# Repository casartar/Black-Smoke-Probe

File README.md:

# Black Smoke Probe

## Einleitung
Die Black Smoke Probe ist eine Open Source Hardware, die kompatibel ist zur Black Magic Probe v2.1e.

Ich habe den letzten öffentlich zugänglichen [Schaltplan](https://black-magic.org/_downloads/5a984c502435264dc19bc5e08c8b55cd/bmpm_v2_1e_schematic.pdf) genommen und die Micro-USB durch eine USB-C Buchse ersetzt. 

Da die Platine leicht von Hand zu bestücken sein sollte, ist das Layout single sided und einige Bauteile als auch die Diemensions der Platine größer gewählt als beim Original. Diesen Maßnahmen ist die UART zum Opfer gefallen und ist nur noch als Testpoints auf der Bottom Seite verfügbar (Ohne Level-Shifter). 

## Original Firmware
[https://github.com/blackmagic-debug/blackmagic](https://github.com/blackmagic-debug/blackmagic)

## iBOM
[ibom.html](https://html-preview.github.io/?url=https://github.com/casartar/Black-Smoke-Probe/blob/main/Hardware/bom/ibom.html)

## Flashen

### Flashen des Bootloaders
```
st-flash write blackmagic_native_bootloader.bin 0x08000000
```

### Flashen der Applikation
```
dfu-util -d 1d50:6018,:6017 -s 0x08002000:leave -D blackmagic_native_firmware.bin
```

## Testen

[https://github.com/casartar/BlackPillUniversalTester](https://github.com/casartar/BlackPillUniversalTester)

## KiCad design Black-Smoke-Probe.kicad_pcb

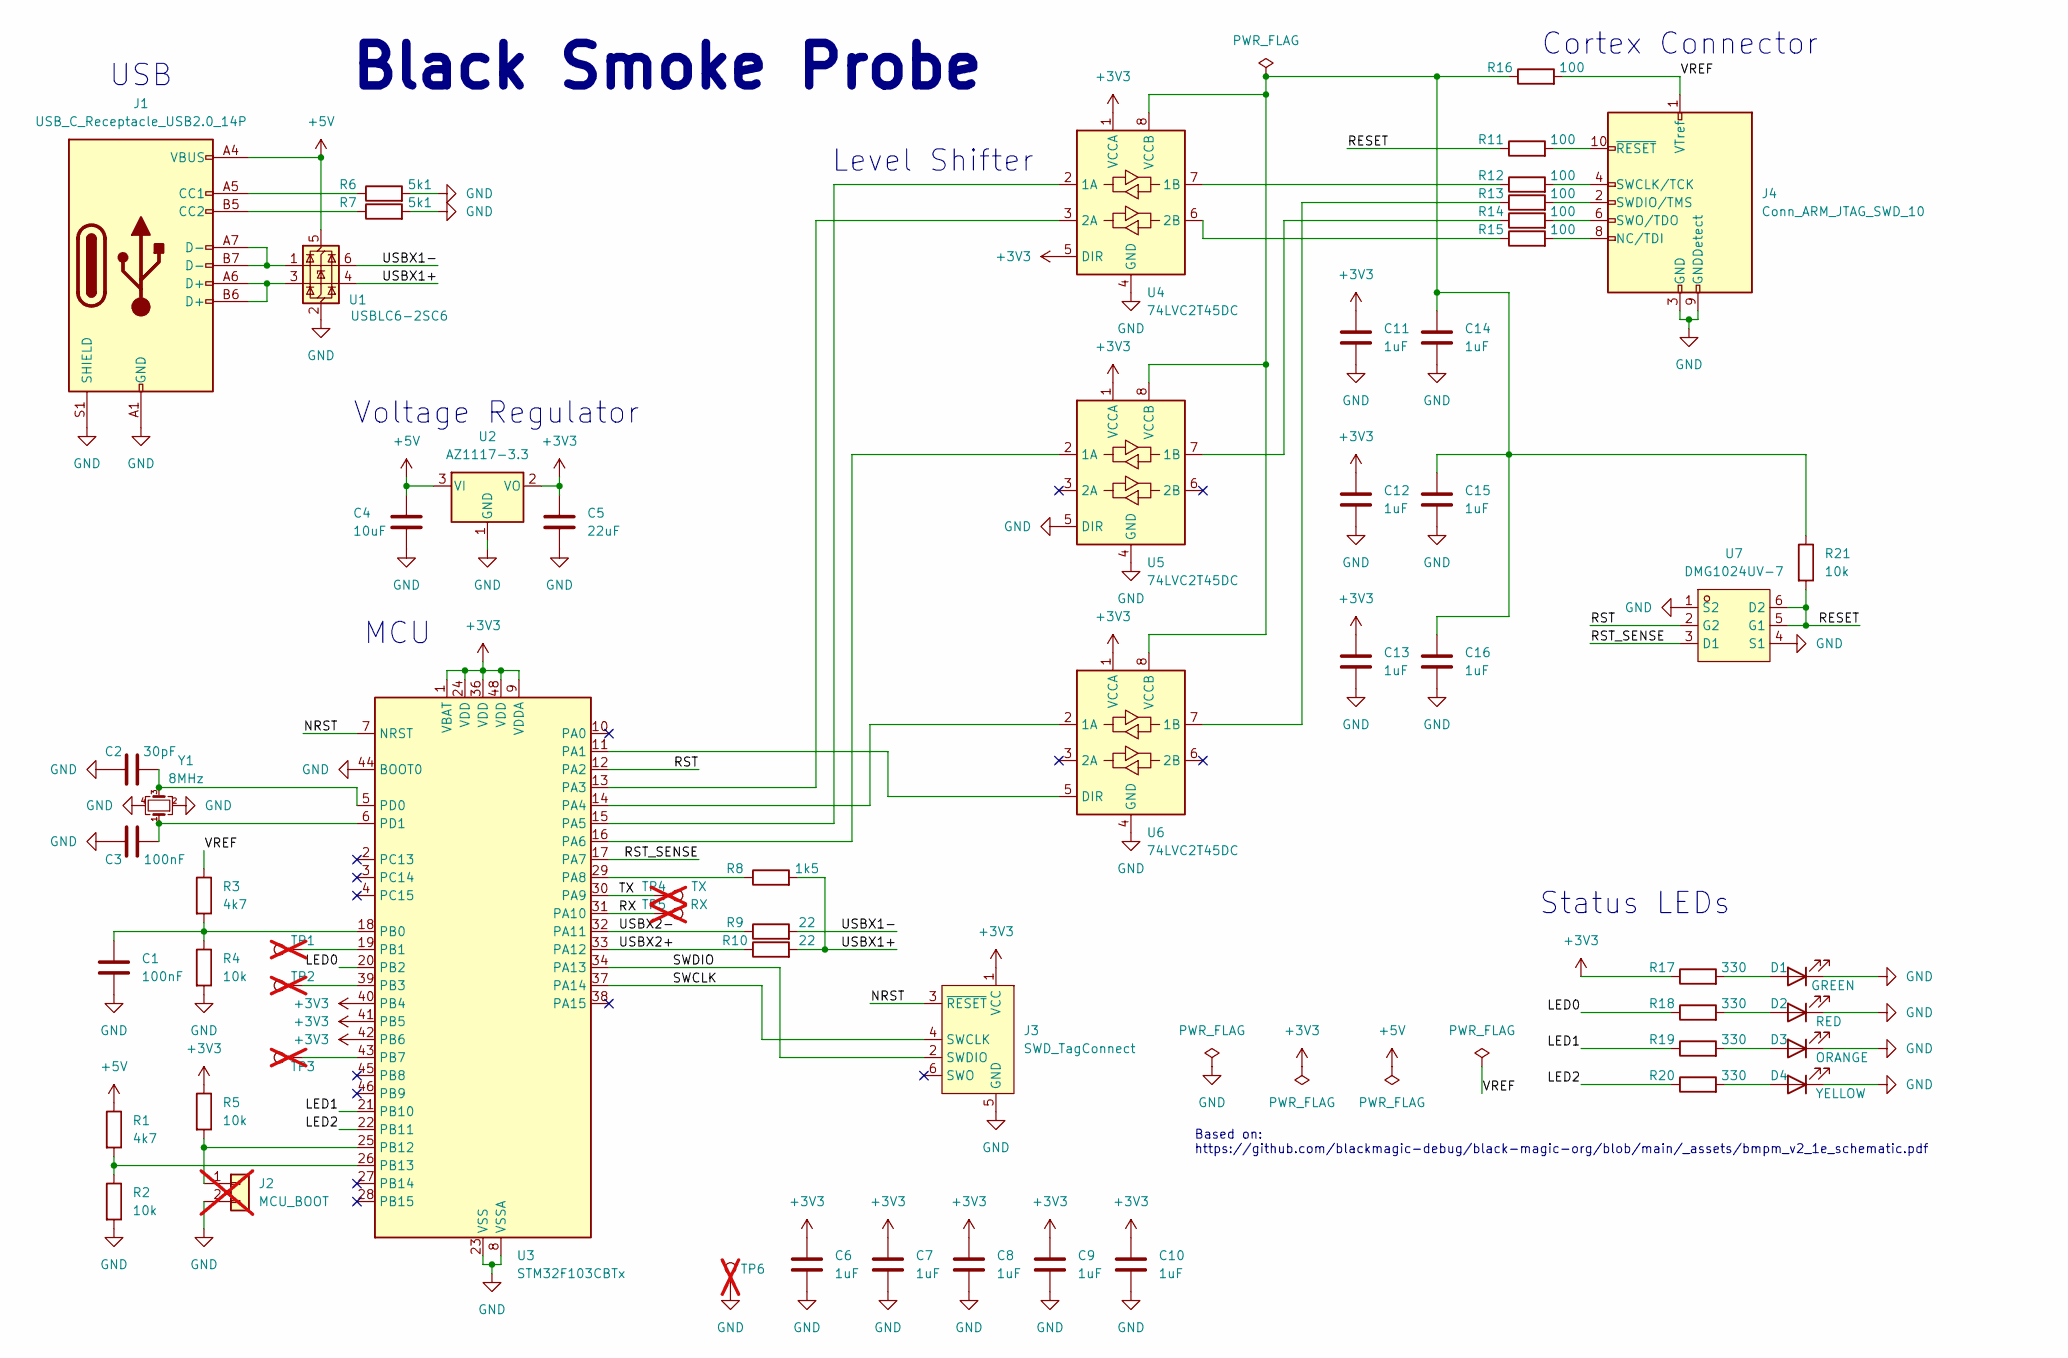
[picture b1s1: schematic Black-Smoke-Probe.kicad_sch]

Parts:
C1, C3: 100nF; C_0603_1608Metric; LCSC Part C14663
C2: 30pF; C_0603_1608Metric; LCSC Part C1658
C4: 10uF; C_0603_1608Metric; LCSC Part C19702
C5: 22uF; C_0603_1608Metric; LCSC Part C86295
C6, C7, C8, C9, C10, C11, C12, C13, C14, C15, C16: 1uF; C_0603_1608Metric; LCSC Part C15849
D1: GREEN; LED_0603_1608Metric; LCSC Part C12065
D2: RED; LED_0603_1608Metric; LCSC Part C157741
D3: ORANGE; LED_0603_1608Metric; LCSC Part C157740
D4: YELLOW; LED_0603_1608Metric; LCSC Part C160477
J1: USB_C_Receptacle_USB2.0_14P; USB_C_Receptacle_HRO_TYPE-C-31-M-12; LCSC Part C165948
J2: MCU_BOOT; PinHeader_1x02_P2.54mm_Vertical; not fitted
J3: SWD_TagConnect; Tag-Connect_TC2030-IDC-NL_2x03_P1.27mm_Vertical
J4: Conn_ARM_JTAG_SWD_10; PinHeader_2x05_P1.27mm_Vertical_SMD; LCSC Part C42372555
R1, R3: 4k7; R_0603_1608Metric; LCSC Part C105428
R2, R4, R5, R21: 10k; R_0603_1608Metric; LCSC Part C98220
R6, R7: 5k1; R_0603_1608Metric; LCSC Part C105580
R8: 1k5; R_0603_1608Metric; LCSC Part C22843
R9, R10: 22; R_0603_1608Metric; LCSC Part C1203
R11, R12, R13, R14, R15, R16: 100; R_0603_1608Metric; LCSC Part C105588
R17, R18, R19, R20: 330; R_0603_1608Metric; LCSC Part C105881
TP1, TP2, TP3, TP6: TestPoint; TestPoint_Pad_D1.0mm; not fitted
TP4: TX; TestPoint_Pad_D1.0mm; not fitted
TP5: RX; TestPoint_Pad_D1.0mm; not fitted
U1: USBLC6-2SC6; SOT-23-6; LCSC Part C2827654
U2: AZ1117-3.3; SOT-89-3; LCSC Part C460428
U3: STM32F103CBTx; LQFP-48_7x7mm_P0.5mm; LCSC Part C8304
U4, U5, U6: 74LVC2T45DC; VSSOP-8_2.3x2mm_P0.5mm; LCSC Part C15741
U7: DMG1024UV-7; SOT-563-6_L1.6-W1.2-P0.5-LS1.6-BL; LCSC Part C2759893
Y1: 8MHz; Crystal_SMD_3225-4Pin_3.2x2.5mm; LCSC Part C2682775

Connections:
+3V3: C5.1, C6.1, C7.1, C8.1, C9.1, C10.1, C11.1, C12.1, C13.1, J3.1 (VCC), R5.1, R17.1, U2.2 (VO), U3.1 (VBAT), U3.9 (VDDA), U3.24 (VDD), U3.36 (VDD), U3.40 (PB4), U3.41 (PB5), U3.42 (PB6), U3.48 (VDD), U4.1 (VCCA), U4.5 (DIR), U5.1 (VCCA), U6.1 (VCCA)
+5V: C4.1, J1.A4 (VBUS), J1.A9 (VBUS), J1.B4 (VBUS), J1.B9 (VBUS), R1.1, U1.5 (VBUS), U2.3 (VI)
/LED0: R18.1, U3.20 (PB2)
/LED1: R19.1, U3.21 (PB10)
/LED2: R20.1, U3.22 (PB11)
/NRST: J3.3 (~RESET), U3.7 (NRST)
/RESET: R11.1, R21.2, U7.5 (G1), U7.6 (D2)
/RST: U3.12 (PA2), U7.2 (G2)
/RST_SENSE: U3.17 (PA7), U7.3 (D1)
/RX: TP5.1, U3.31 (PA10)
/SWCLK: J3.4 (SWCLK), U3.37 (PA14)
/SWDIO: J3.2 (SWDIO), U3.34 (PA13)
/TX: TP4.1, U3.30 (PA9)
/USBX1+: R8.2, R10.2, U1.4 (I/O2)
/USBX1-: R9.2, U1.6 (I/O1)
/USBX2+: R10.1, U3.33 (PA12)
/USBX2-: R9.1, U3.32 (PA11)
/VREF: J4.1 (VTref), R3.1, R16.2
GND: C1.2, C2.2, C3.1, C4.2, C5.2, C6.2, C7.2, C8.2, C9.2, C10.2, C11.2, C12.2, C13.2, C14.2, C15.2, C16.2, D1.1 (K), D2.1 (K), D3.1 (K), D4.1 (K), J1.A1 (GND), J1.A12 (GND), J1.B1 (GND), J1.B12 (GND), J1.S1 (SHIELD), J2.2, J3.5 (GND), J4.3 (GND), J4.5 (GND), J4.9 (GNDDetect), R2.2, R4.2, R6.2, R7.2, TP6.1, U1.2 (GND), U2.1 (GND), U3.8 (VSSA), U3.23 (VSS), U3.35 (VSS), U3.44 (BOOT0), U3.47 (VSS), U4.4 (GND), U5.4 (GND), U5.5 (DIR), U6.4 (GND), U7.1 (S2), U7.4 (S1), Y1.2, Y1.4
unnamed: D1.2 (A), R17.2
unnamed: D2.2 (A), R18.2
unnamed: D3.2 (A), R19.2
unnamed: D4.2 (A), R20.2
unnamed: J1.A5 (CC1), R6.1
unnamed: J1.B5 (CC2), R7.1
unnamed: J1.A6 (D+), J1.B6 (D+), U1.3 (I/O2)
unnamed: J1.A7 (D-), J1.B7 (D-), U1.1 (I/O1)
unnamed: J2.1, R5.2, U3.25 (PB12)
unnamed: J4.8 (NC/TDI), R15.2
unnamed: J4.4 (SWCLK/TCK), R12.2
unnamed: J4.2 (SWDIO/TMS), R13.2
unnamed: J4.6 (SWO/TDO), R14.2
unnamed: J4.10 (~RESET), R11.2
unnamed: U3.11 (PA1), U6.5 (DIR)
unnamed: U3.13 (PA3), U4.3 (2A)
unnamed: U3.14 (PA4), U6.2 (1A)
unnamed: U3.15 (PA5), U4.2 (1A)
unnamed: U3.16 (PA6), U5.2 (1A)
unnamed: R8.1, U3.29 (PA8)
unnamed: C1.1, R3.2, R4.1, U3.18 (PB0)
unnamed: TP1.1, U3.19 (PB1)
unnamed: TP2.1, U3.39 (PB3)
unnamed: TP3.1, U3.43 (PB7)
unnamed: R1.2, R2.1, U3.26 (PB13)
unnamed: C2.1, U3.5 (PD0), Y1.3
unnamed: C3.2, U3.6 (PD1), Y1.1
unnamed: R12.1, U4.7 (1B)
unnamed: R15.1, U4.6 (2B)
unnamed: C14.1, C15.1, C16.1, R16.1, R21.1, U4.8 (VCCB), U5.8 (VCCB), U6.8 (VCCB)
unnamed: R14.1, U5.7 (1B)
unnamed: R13.1, U6.7 (1B)

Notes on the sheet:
Status LEDs
Based on: https://github.com/blackmagic-debug/black-magic-org/blob/main/_assets/bmpm_v2_1e_schematic.pdf
Cortex Connector
Voltage Regulator
MCU
Level Shifter
Black Smoke Probe
USB

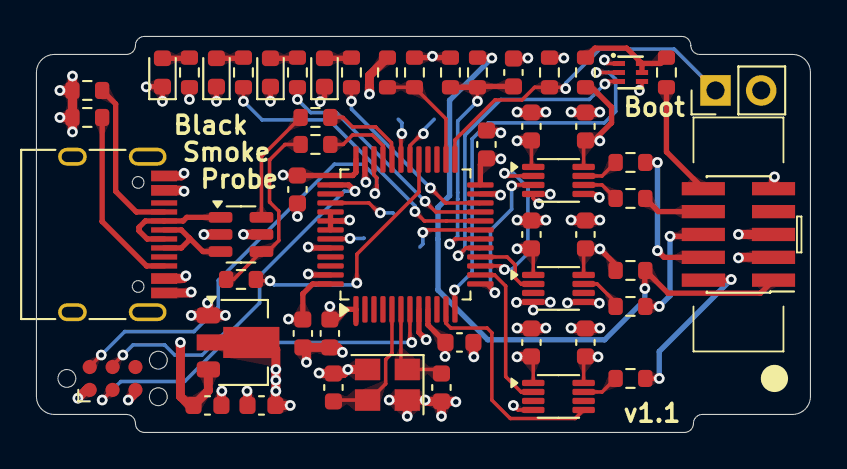
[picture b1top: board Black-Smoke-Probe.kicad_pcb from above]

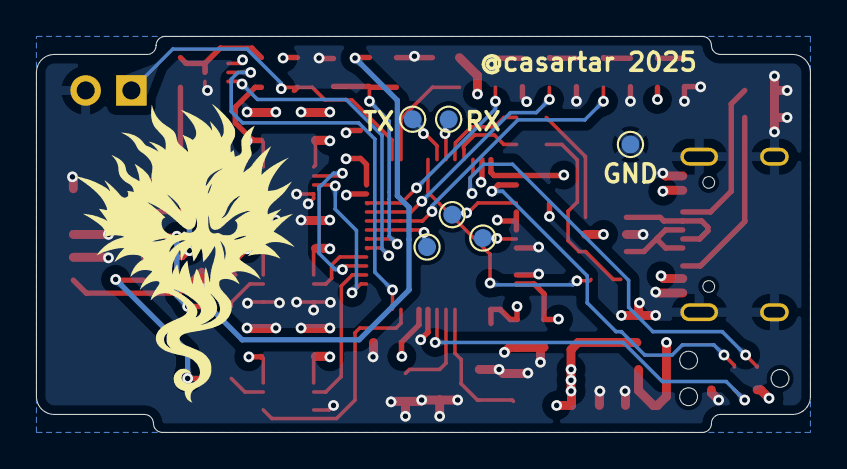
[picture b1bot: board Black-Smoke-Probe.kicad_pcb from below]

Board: 4 copper layers, 43.0 x 22.0 mm, 59 parts (6 on the bottom side), 51 nets.

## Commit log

2025-03-26 initial commit v1.0
2025-04-08 first changes for v1.1
    - schematic corrections
    - new layout with 4 layer PCB
2025-04-08 bom, schematic, drc corrections and add logo
2025-04-09 corrections
2025-04-09 remove top gnd plane
2025-04-09 add license
2025-04-11 add v1.1 production files
2025-04-11 add schematic pdf
2025-04-11 add ibom
2025-04-14 v1.1.1 changed capacitor from 100nf to 30pf
2025-07-22 change folder structure and update readme

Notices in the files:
Black-Smoke-Probe.kicad_sch:
License: CC-BY-SA 4.0
